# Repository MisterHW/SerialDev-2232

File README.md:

## SerialDev-2232 ##
The SerialDev-2232 board is a 50 x 50 mm² prototyping PCB with a FTDI FT2232HQ USB interface IC, 12 MHz oscillator and 3.3V, 1.2V LDOs. 

It breaks out the two Multi-Protocol Synchronous Serial Engine (MPSSE) ports, one particularly labeled as a JTAG / SPI / UART port, the other one as a full 16 I/O interface including the 8 bit parallel 245 type FIFO / bit banging interface.

Half of the PCB is dedicated to 5V, 3.3V, 1.2V supplies, 12 MHz clock source and a fully implemented FT2232H with EEPROM, all of which also feed into a linear header (cut the PCB in half for breadboard depolyment). The rest is just 0.1" perf board. 

### assembled PCB ###

### schematic ###

### layout ###

### further information ###

For more please also check out https://hackaday.io/project/9902-serial-dev-2232.

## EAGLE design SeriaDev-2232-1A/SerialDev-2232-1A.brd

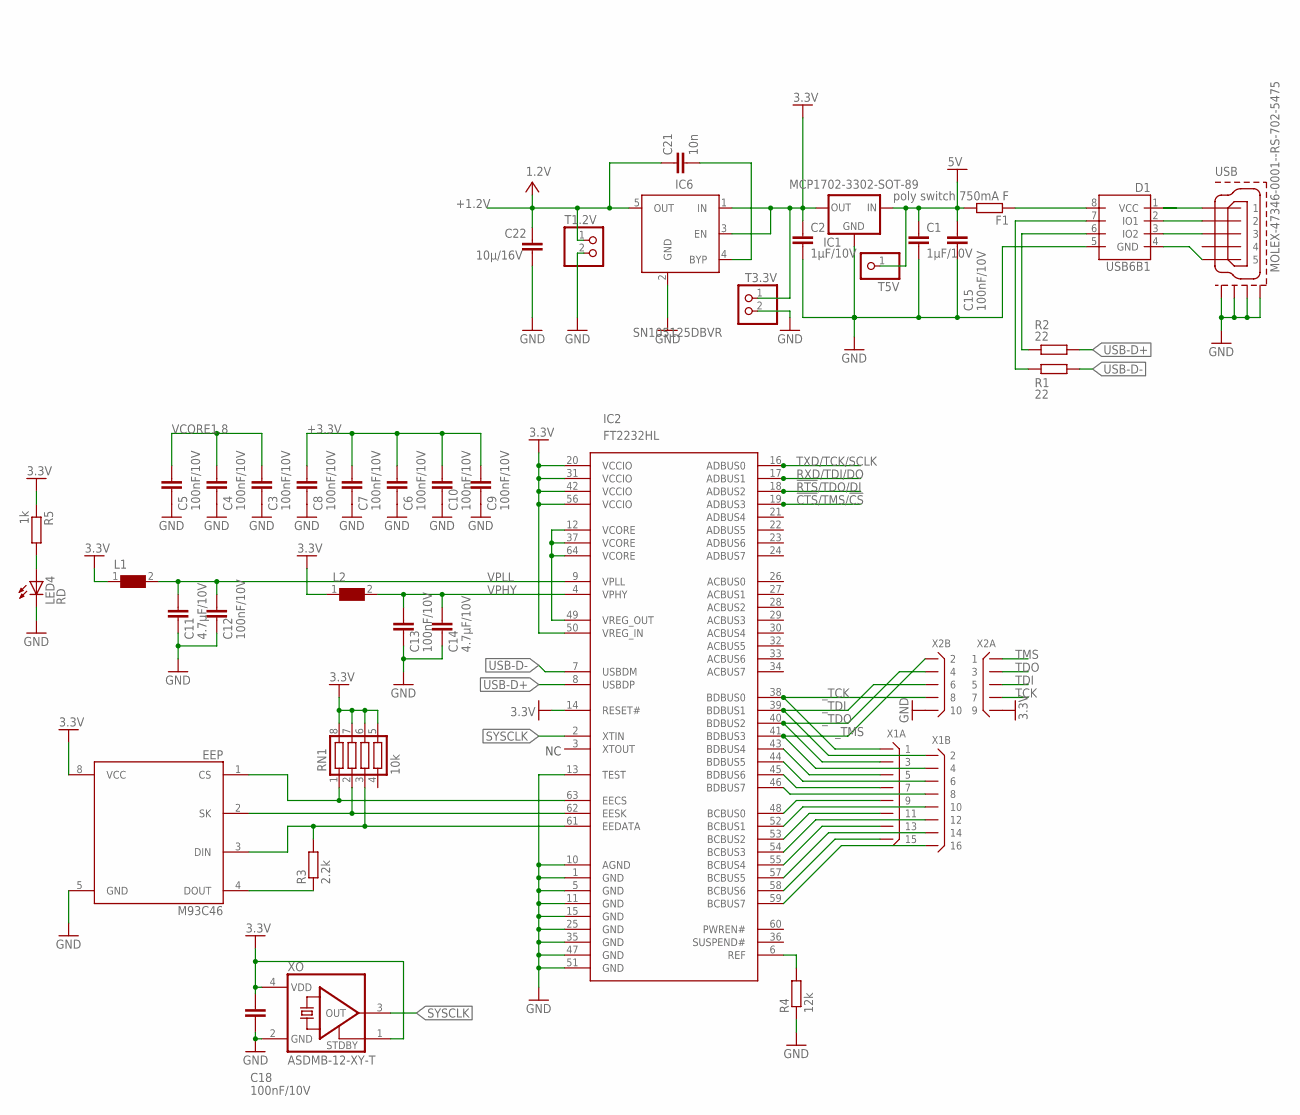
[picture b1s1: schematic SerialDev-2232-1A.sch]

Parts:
C1, C2: 1µF/10V; C0805K
C3, C4, C5, C6, C7, C8, C9, C10, C12, C13, C15, C18: 100nF/10V; C0402K; MOUSER 810-C1005X7R1H104K
C11, C14: 4.7µF/10V; C0402K; MOUSER 810-C1005X7R1H104K
C21: 10n; C0805K; PARTNO Kemet: C1206C103K5RACTU
C22: 10µ/16V; C0805K; PARTNO Vishay Sprague: TR3B106K016C0800
D1: USB6B1; SO08
EEP: M93C46; SO08
F1: poly switch 750mA F; R1206
IC1: MCP1702-3302-SOT-89; SOT89-R
IC2: FT2232HL; LQFP-ST-64-2
IC6: SN105125DBVR; SOT23-5; PARTNO LINEAR TECHNOLOGY: LT1761ES5-1.2
L1, L2: WE-CBF_0603; 0603
LED4: RD; CHIP-LED0805
R1, R2: 22; R0603
R3: 2.2k; R0603
R4: 12k; R0603
R5: 1k; R0603
RN1: 10k; CTS742C083
T1.2V, T3.3V: PINHD-1X2; 1X02
T5V: PINHD-1X1; 1X01
USB: MOLEX-47346-0001--RS-702-5475; MOLEX-47364-0001
X1: X08X2IR; X16R-IDC
X2: X05X2DR; X10R-DIL
XO: ASDMB-12-XY-T; XO-4-2.5X2.0; MFG_PARTNO ASDMB-12.000MHZ-XY-T; MOUSER 815-ASDMB-12-XY-T

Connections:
!CTS!/TMS/!CS!: IC2.19 (ADBUS3)
!RTS!/TDO/DI: IC2.18 (ADBUS2)
+1.2V: C21.1, C22.1, IC6.5 (OUT), T1.2V.1
+3.3V: C2.1, C6.1, C7.1, C8.1, C9.1, C10.1, C18.1, EEP.8 (VCC), IC1.3 (OUT), IC2.14 (RESET#), IC2.20 (VCCIO), IC2.31 (VCCIO), IC2.42 (VCCIO), IC2.50 (VREG_IN), IC2.56 (VCCIO), IC6.1 (IN), IC6.3 (EN), L1.1, L2.1, R5.1, RN1.5, RN1.6, RN1.7, RN1.8, T3.3V.1, X2.9, XO.1 (TRI), XO.4 (VDD)
+5V: C1.1, C15.1, F1.2, IC1.2 (IN), IC1.4 (IN), T5V.1
GND: C1.2, C2.2, C3.2, C4.2, C5.2, C6.2, C7.2, C8.2, C9.2, C10.2, C11.2, C12.2, C13.2, C14.2, C15.2, C18.2, C22.2, D1.5 (GND), EEP.5 (GND), IC1.1 (GND), IC2.1 (GND), IC2.5 (GND), IC2.10 (AGND), IC2.11 (GND), IC2.13 (TEST), IC2.15 (GND), IC2.25 (GND), IC2.35 (GND), IC2.47 (GND), IC2.51 (GND), IC6.2 (GND), LED4.C, R4.1, T1.2V.2, T3.3V.2, USB.GND1, USB.GND2, USB.GND3, USB.GND4, X2.10, XO.2 (GND)
unnamed: EEP.1 (CS), IC2.63 (EECS), RN1.1
unnamed: D1.6 (IO2), R2.1
unnamed: D1.7 (IO1), R1.2
unnamed: EEP.2 (SK), IC2.62 (EESK), RN1.2
unnamed: EEP.3 (DIN), IC2.61 (EEDATA), R3.2, RN1.3
unnamed: EEP.4 (DOUT), R3.1
unnamed: D1.4 (GND), USB.5
unnamed: D1.3 (IO2), USB.3
unnamed: IC2.6 (REF), R4.2
unnamed: D1.2 (IO1), USB.2
unnamed: D1.8 (VCC), F1.1
unnamed: C21.2, IC6.4 (BYP)
unnamed: LED4.A, R5.2
unnamed: IC2.43 (BDBUS4), X1.5
unnamed: IC2.44 (BDBUS5), X1.6
unnamed: IC2.45 (BDBUS6), X1.7
unnamed: IC2.46 (BDBUS7), X1.8
unnamed: IC2.48 (BCBUS0), X1.9
unnamed: IC2.52 (BCBUS1), X1.10
unnamed: IC2.53 (BCBUS2), X1.11
unnamed: IC2.54 (BCBUS3), X1.12
unnamed: IC2.55 (BCBUS4), X1.13
unnamed: IC2.57 (BCBUS5), X1.14
unnamed: IC2.58 (BCBUS6), X1.15
unnamed: IC2.59 (BCBUS7), X1.16
RXD/TDI/DO: IC2.17 (ADBUS1)
SYSCLK: IC2.2 (XTIN), XO.3 (OUT)
TCK: X2.7
TDI: X2.5
TDO: X2.3
TMS: X2.1
TXD/TCK/SCLK: IC2.16 (ADBUS0)
USB-D+: IC2.8 (USBDP), R2.2
USB-D-: IC2.7 (USBDM), R1.1
USB_5V: D1.1 (VCC), USB.1
VCORE1.8: C3.1, C4.1, C5.1, IC2.12 (VCORE), IC2.37 (VCORE), IC2.49 (VREG_OUT), IC2.64 (VCORE)
VPHY: C13.1, C14.1, IC2.4 (VPHY), L2.2
VPLL: C11.1, C12.1, IC2.9 (VPLL), L1.2
_TCK: IC2.38 (BDBUS0), X1.1, X2.8
_TDI: IC2.39 (BDBUS1), X1.2, X2.6
_TDO: IC2.40 (BDBUS2), X1.3, X2.4
_TMS: IC2.41 (BDBUS3), X1.4, X2.2

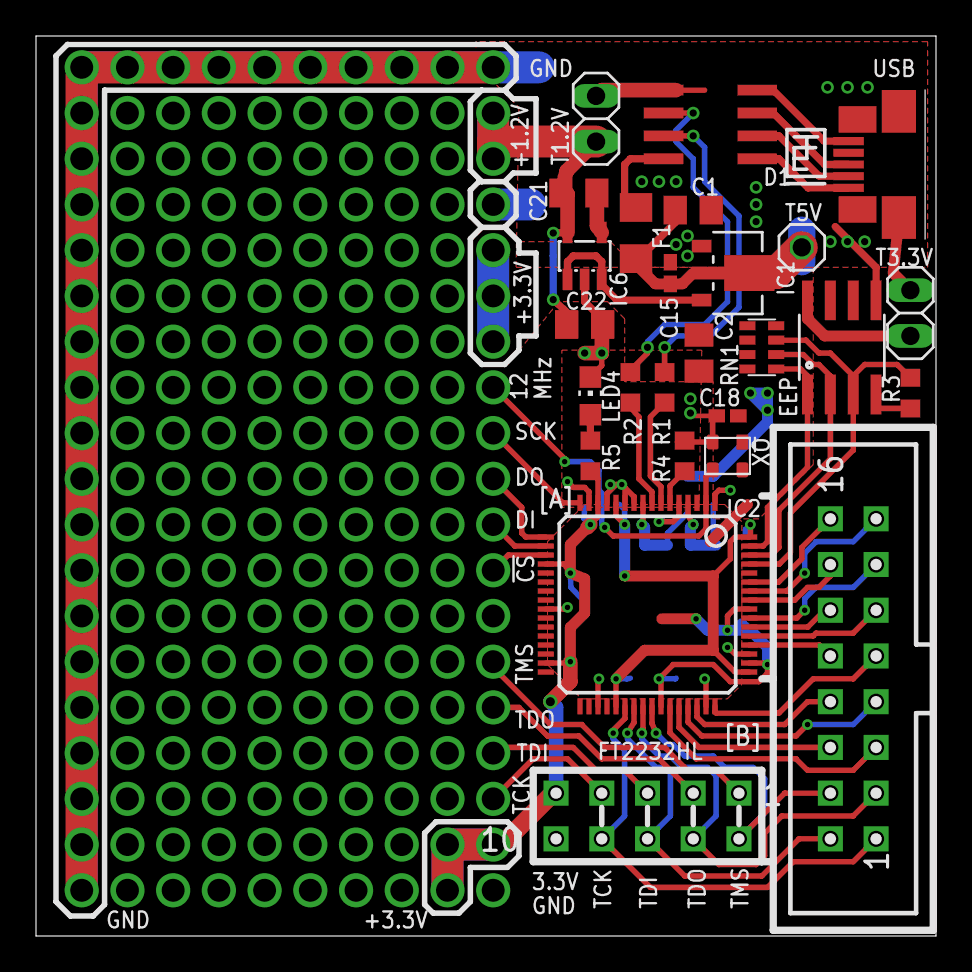
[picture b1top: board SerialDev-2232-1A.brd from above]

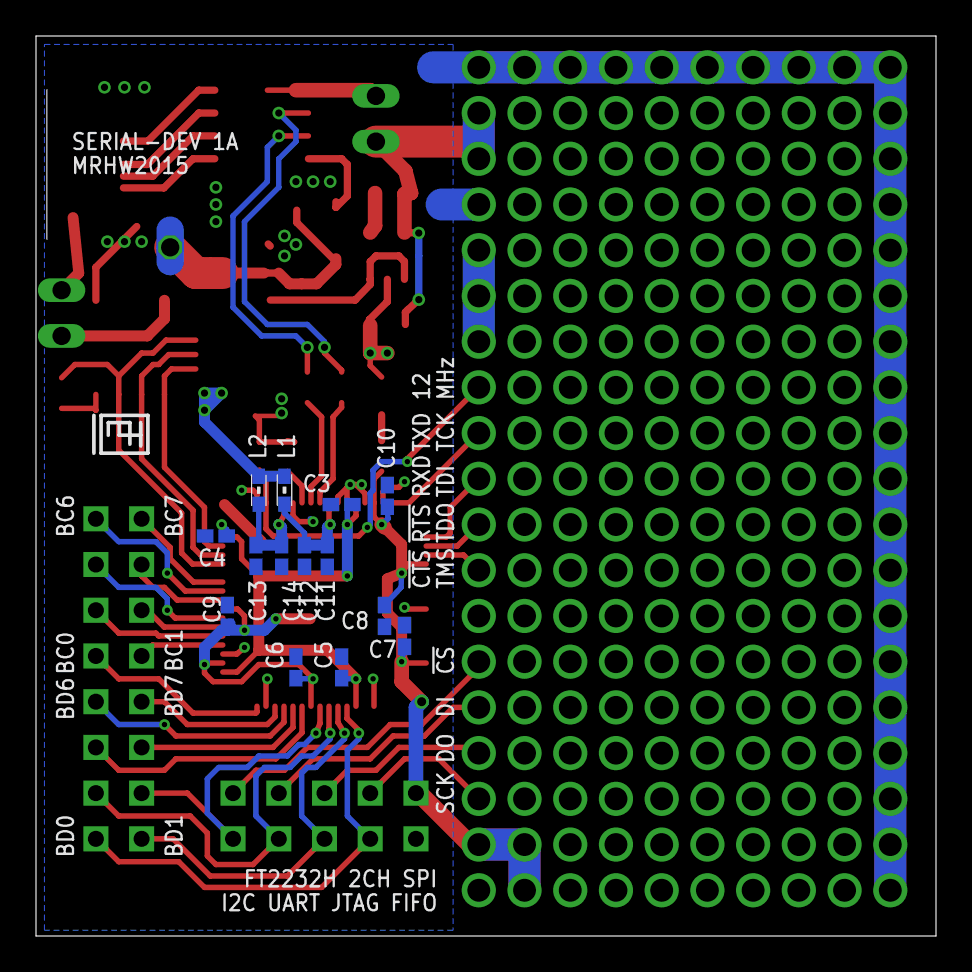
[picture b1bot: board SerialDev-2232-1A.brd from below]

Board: 2 copper layers, 50.0 x 50.0 mm, 42 parts (15 on the bottom side), 40 nets.

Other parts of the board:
U$1, U$2: DESIGNER

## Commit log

2018-02-11 initial commit of hardware iteration 1A (built and tested, seems ok)
2018-02-11 Create README.md
    The SerialDev-2232 board is a 50 x 50 mm² PCB that breaks out the two MPSSE ports, one as a JTAG / SPI / UART port, the other one as a fully featured MPSSE interface including the 8 bit parallel 245 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
    Half of the PCB is dedicated to 5V, 3.3V, 1.2V supplies, 12 MHz clock source and a fully implemented FT2232H with EEPROM, all of which also feed into a linear header (cut the PCB in half for breadboa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
    for more please also check out https://hackaday.io/project/9902-serial-dev-2232
2019-01-02 add schematic png
2020-06-27 added documentation.
2020-06-27 remove duplicate doc/, add gerber files.
2020-06-27 added BOM

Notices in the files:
parts and their libraries:
SparkFun-DigitalIC: Licensing: CC v3.0 Share-Alike You are welcome to use this library for commercial purposes.
EagleLibrary_Wuerth_Elektronik_eiSos_V6_: Copyright: Würth Elektronik
